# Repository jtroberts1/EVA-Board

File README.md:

# EVA-Board
Simple PCB Board for EVA HotEnd.  Uses JST-XH and JSF-VH connectors

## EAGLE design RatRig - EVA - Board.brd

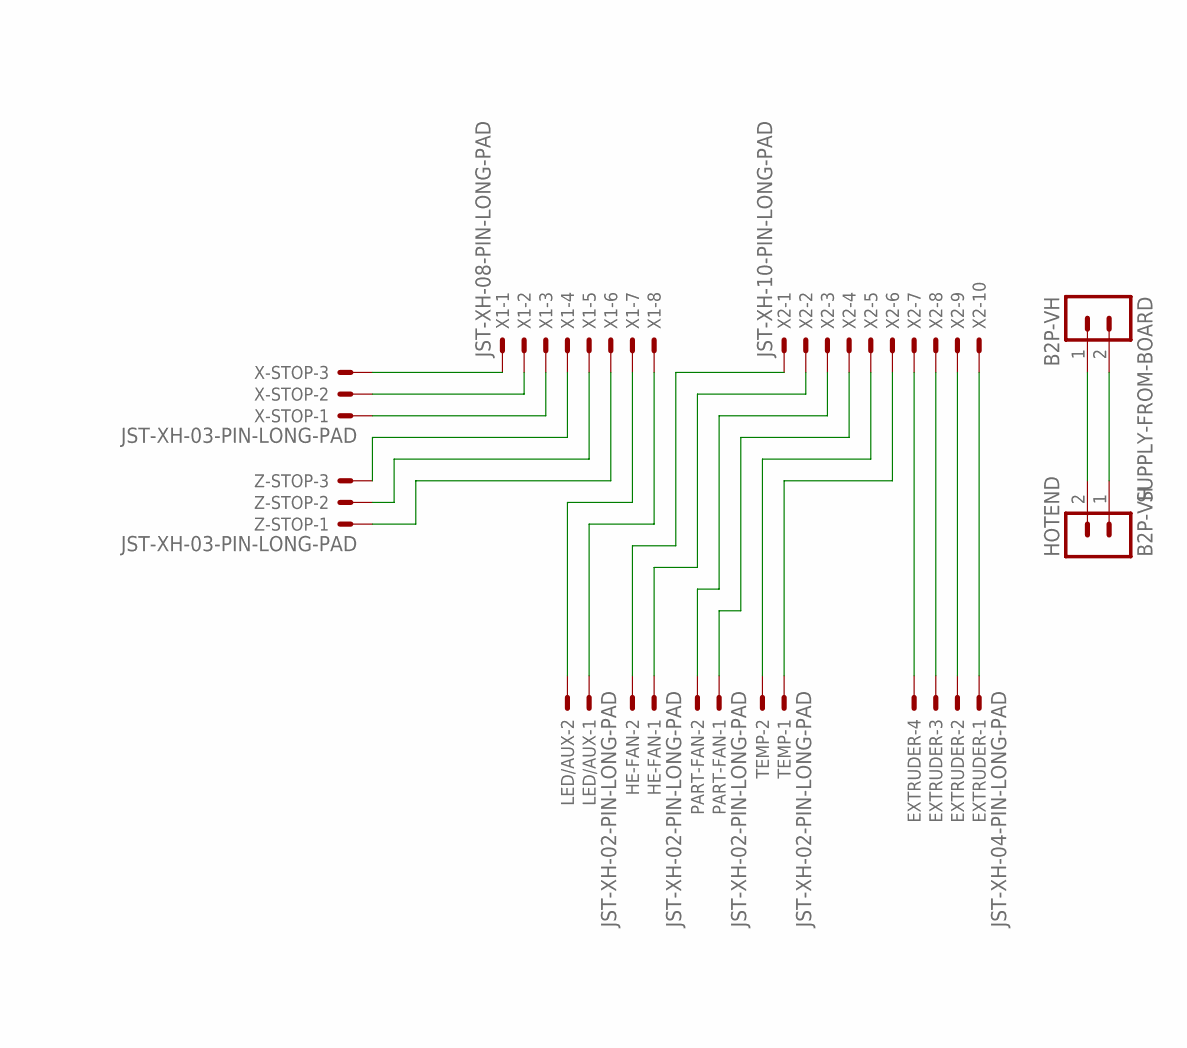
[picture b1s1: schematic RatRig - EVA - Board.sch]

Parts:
EXTRUDER: JST-XH-04-PIN-LONG-PAD; JST-XH-04-PACKAGE-LONG-PAD
HE-FAN: JST-XH-02-PIN-LONG-PAD; JST-XH-02-PACKAGE-LONG-PAD
HOTEND: B2P-VH
LED/AUX: JST-XH-02-PIN-LONG-PAD; JST-XH-02-PACKAGE-LONG-PAD
PART-FAN: JST-XH-02-PIN-LONG-PAD; JST-XH-02-PACKAGE-LONG-PAD
SUPPLY-FROM-BOARD: B2P-VH
TEMP: JST-XH-02-PIN-LONG-PAD; JST-XH-02-PACKAGE-LONG-PAD
X1: JST-XH-08-PIN-LONG-PAD; JST-XH-08-PACKAGE-LONG-PAD
X2: JST-XH-10-PIN-LONG-PAD; JST-XH-10-PACKAGE-LONG-PAD
X-STOP: JST-XH-03-PIN-LONG-PAD; JST-XH-03-PACKAGE-LONG-PAD
Z-STOP: JST-XH-03-PIN-LONG-PAD; JST-XH-03-PACKAGE-LONG-PAD

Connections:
HE-FAN-GND: HE-FAN.1, X2.2
HE-FAN-VCC: HE-FAN.2, X2.1
HE-GND: HOTEND.1, SUPPLY-FROM-BOARD.2
HE-VCC: HOTEND.2, SUPPLY-FROM-BOARD.1
LED-5V: LED/AUX.2, X1.7
LED-GND: LED/AUX.1, X1.8
MOTOR-1: EXTRUDER.4, X2.7
MOTOR-2: EXTRUDER.3, X2.8
MOTOR-3: EXTRUDER.2, X2.9
MOTOR-4: EXTRUDER.1, X2.10
PART-FAN-GND: PART-FAN.1, X2.4
PART-FAN-VCC: PART-FAN.2, X2.3
TEMP-P1: TEMP.2, X2.5
TEMP-P2: TEMP.1, X2.6
X-5V: X1.3, X-STOP.1
X-GND: X1.2, X-STOP.2
X-SIG: X1.1, X-STOP.3
Z-5V: X1.6, Z-STOP.1
Z-GND: X1.5, Z-STOP.2
Z-SIG: X1.4, Z-STOP.3

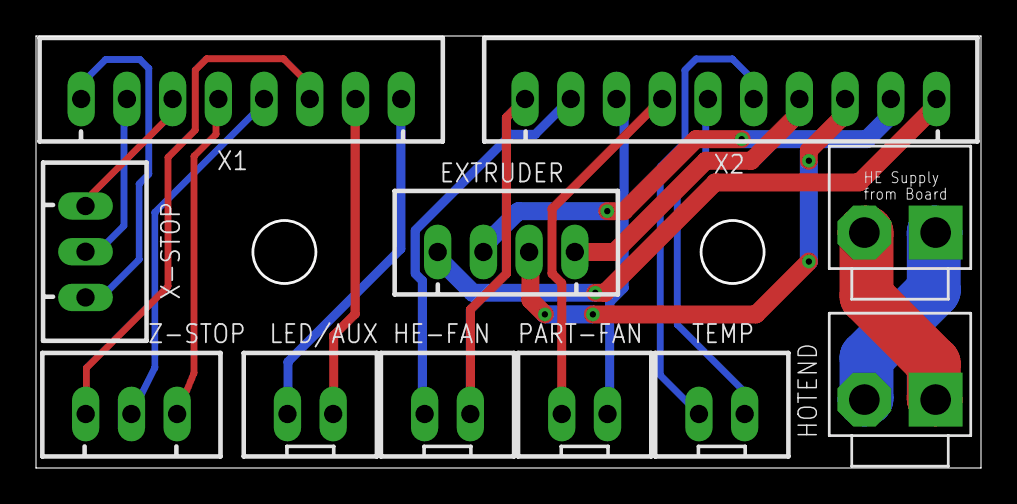
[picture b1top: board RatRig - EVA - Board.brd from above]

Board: 2 copper layers, 52.3 x 23.8 mm, 11 parts (0 on the bottom side), 20 nets.
